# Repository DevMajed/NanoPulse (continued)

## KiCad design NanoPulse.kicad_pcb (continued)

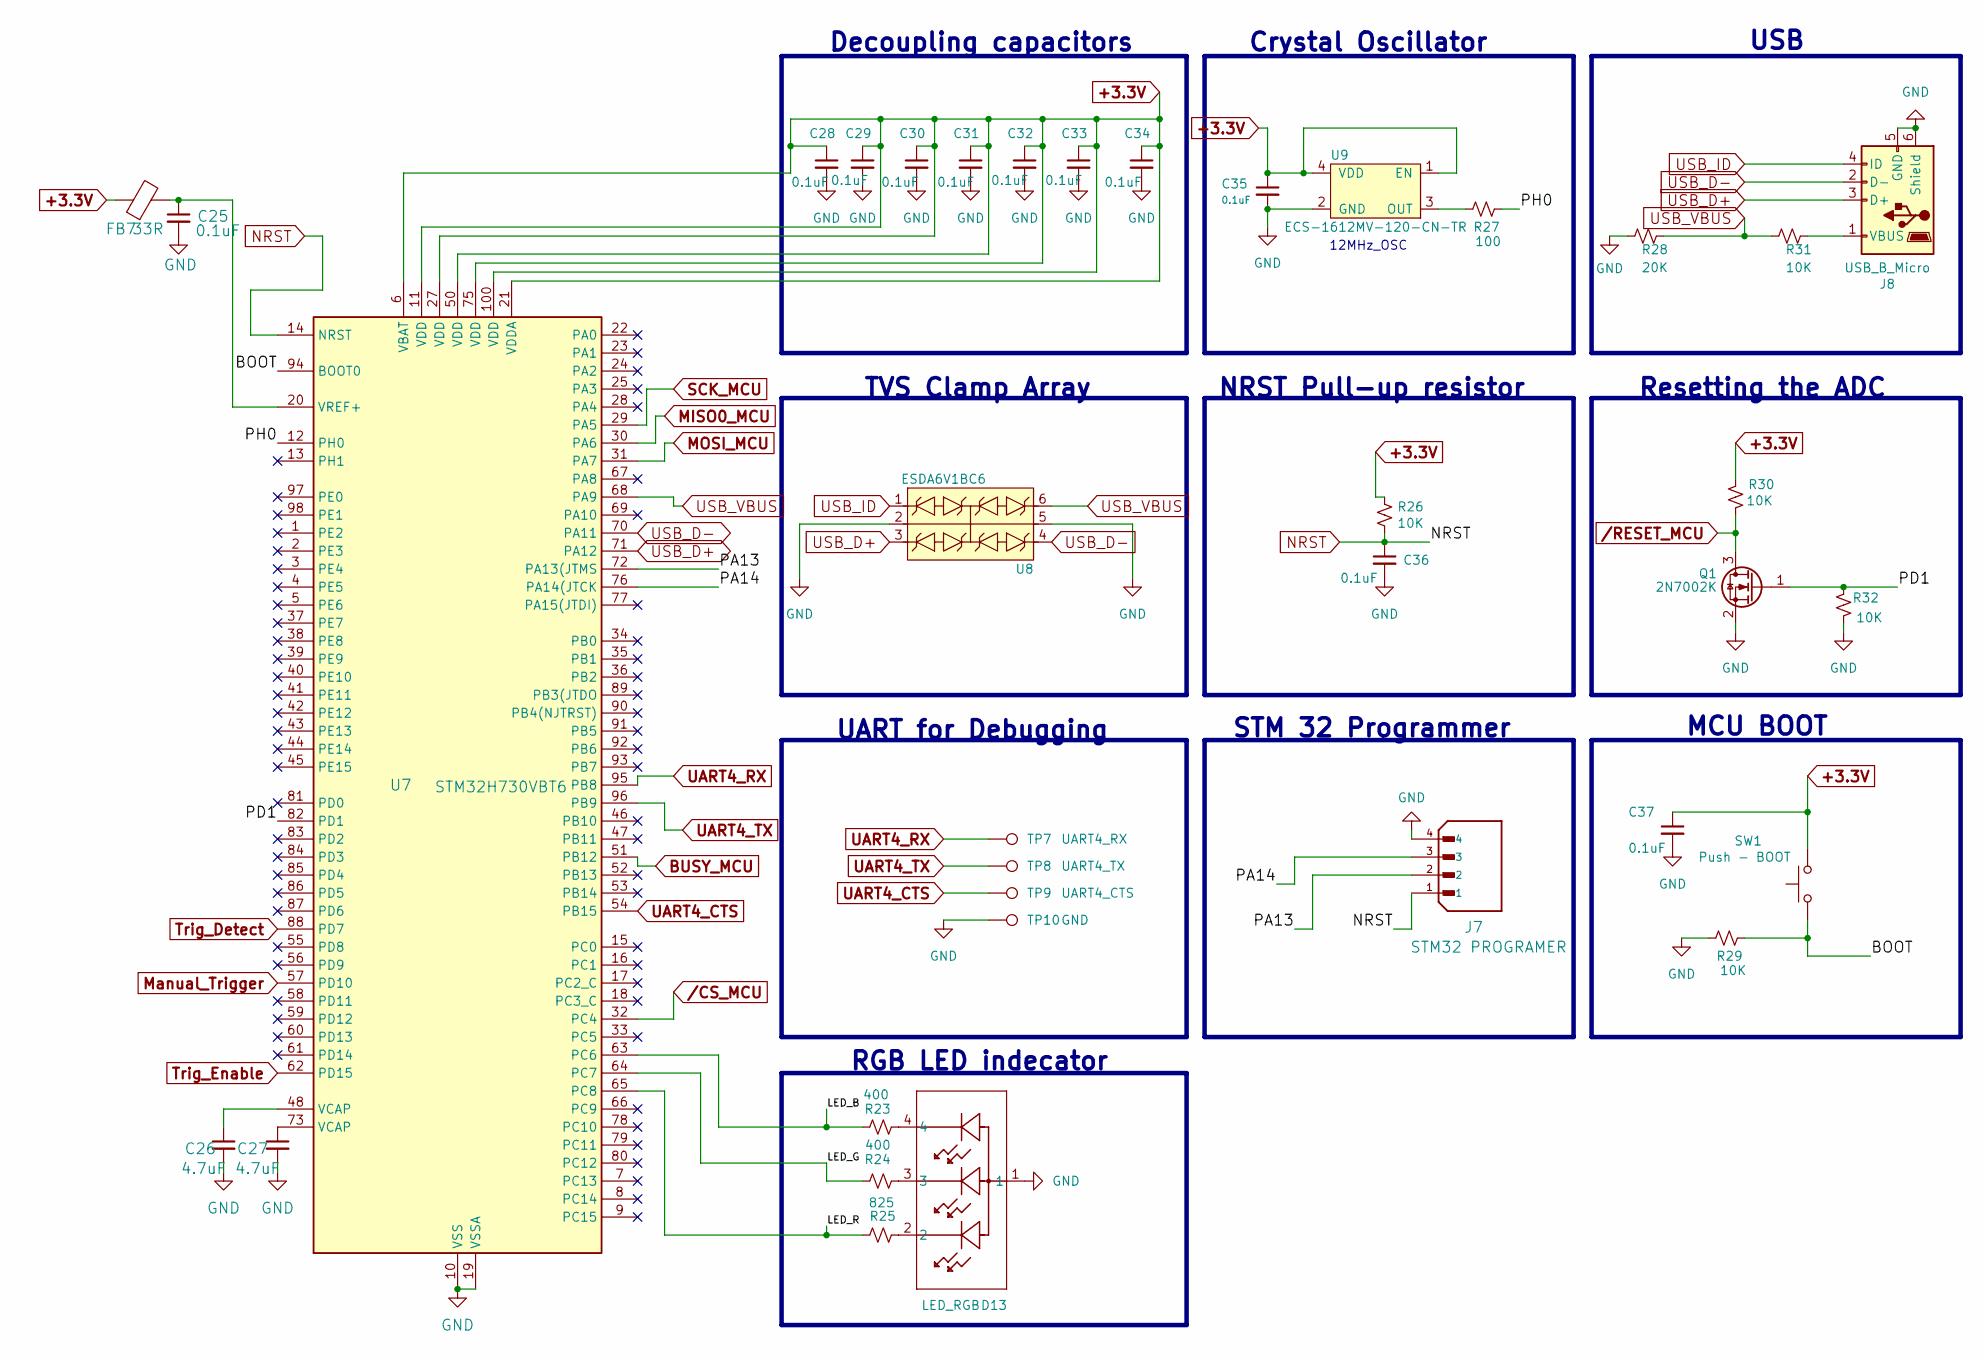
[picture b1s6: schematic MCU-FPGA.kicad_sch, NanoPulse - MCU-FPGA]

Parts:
C25, C28, C29, C30, C31, C32, C33, C34, C35, C36, C37: 0.1uF; C_0603_1608Metric; Mfg part # CC0603KRX7R7BB104; Digikey 311-1088-1-ND
C26, C27: 4.7uF; C_0805_2012Metric; Mfg part # CL21A475KAQNNNE; Digikey 1276-1244-1-ND
D13: LED_RGB; APHF1608SEEQBDZGKC_KNB-L; Mfg part # APHF1608SEEQBDZGKC; Digikey 754-2144-2-ND
FB7: 33R; L_0603_1608Metric_Pad1.05x0.95mm_HandSolder; Mfg part # BLM18PG330SN1D; Digikey 490-5220-1-ND
J7: STM32 PROGRAMER; SPARKFUN_PRT-14417; PARTREV NA; Digikey 1568-14417-ND
J8: USB_B_Micro; USB_Micro-B_Molex-105017-0001; Mfg part # 0473461001; Digikey WM11228CT-ND
Q1: 2N7002K; SOT-23; Mfg part # 2N7002LT1G; Digikey 2N7002LT1GOSCT-ND
R23, R24: 400; R_0603_1608Metric; Mfg part # PAT0603E4000BST1; Digikey PAT400ACT-ND
R25: 825; R_0603_1608Metric; Mfg part # RC0603FR-07825RL; Digikey 311-825HRCT-ND
R26, R29, R30, R31, R32: 10K; R_0603_1608Metric; Mfg part # RC0603FR-0710KL; Digikey 311-10.0KHRCT-ND
R27: 100; R_0603_1608Metric; Mfg part # RC0603FR-07100RL; Digikey 311-100HRCT-ND
R28: 20K; R_0603_1608Metric; Mfg part # RC0603FR-0720KL; Digikey 311-20.0KHRCT-ND
SW1: Push - BOOT; SW_Tactile_SPST_NO_Straight_CK_PTS636Sx25SMTRLFS; Mfg part # TL59NF160Q; Digikey EG2532CT-ND
TP7: UART4_RX; TestPoint_Pad_1.0x1.0mm
TP8: UART4_TX; TestPoint_Pad_1.0x1.0mm
TP9: UART4_CTS; TestPoint_Pad_1.0x1.0mm
TP10: GND; TestPoint_Pad_1.0x1.0mm
U7: STM32H730VBT6; LQFP-100_14x14mm_P0.5mm; Mfg part # STM32H730VBT6; Digikey 497-STM32H730VBT6-ND
U8: ESDA6V1BC6; SOT-23-6; Mfg part # STMicroelectronics; Digikey 497-6635-1-ND
U9: ECS-1612MV-120-CN-TR; Mfg part # ECS-1612MV-120-CN-TR; Digikey XC2833CT-ND

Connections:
+3.3V: C28.1, C29.1, C30.1, C31.1, C32.1, C33.1, C34.1, C35.1, C37.1, FB7.1, R26.1, R30.1, SW1.2, U7.6 (VBAT), U7.11 (VDD), U7.21 (VDDA), U7.27 (VDD), U7.50 (VDD), U7.75 (VDD), U7.100 (VDD), U9.1 (EN), U9.4 (VDD); also elsewhere on the board
/MCU-FPGA/BOOT: R29.1, SW1.1, U7.94 (BOOT0)
/MCU-FPGA/LED_B: R23.1, U7.63 (PC6)
/MCU-FPGA/LED_G: R24.1, U7.64 (PC7)
/MCU-FPGA/LED_R: R25.1, U7.65 (PC8)
/MCU-FPGA/PA13: J7.2, U7.72 (PA13(JTMS)
/MCU-FPGA/PA14: J7.3, U7.76 (PA14(JTCK)
/MCU-FPGA/PD1: Q1.1 (G), R32.1, U7.82 (PD1)
/MCU-FPGA/PH0: R27.1, U7.12 (PH0)
BUSY_MCU: U7.51 (PB12); also elsewhere on the board
GND: C25.2, C26.2, C27.2, C28.2, C29.2, C30.2, C31.2, C32.2, C33.2, C34.2, C35.2, C36.2, C37.2, D13.1, J7.4, J8.5 (GND), J8.6 (Shield), Q1.2 (S), R28.2, R29.2, R32.2, TP10.1, U7.10 (VSS), U7.19 (VSSA), U7.26 (VSS), U7.49 (VSS), U7.74 (VSS), U7.99 (VSS), U8.2, U8.5, U9.2 (GND); also elsewhere on the board
MISO0_MCU: U7.30 (PA6); also elsewhere on the board
MOSI_MCU: U7.31 (PA7); also elsewhere on the board
Manual_Trigger: U7.57 (PD10); also elsewhere on the board
NRST: C36.1, J7.1, R26.2, U7.14 (NRST)
unnamed: C26.1, U7.48 (VCAP)
unnamed: C27.1, U7.73 (VCAP)
unnamed: D13.2, R25.2
unnamed: D13.3, R24.2
unnamed: D13.4, R23.2
unnamed: J8.1 (VBUS), R31.1
unnamed: C25.1, FB7.2, U7.20 (VREF+)
unnamed: R27.2, U9.3 (OUT)
SCK_MCU: U7.29 (PA5); also elsewhere on the board
Trig_Detect: U7.88 (PD7); also elsewhere on the board
Trig_Enable: U7.62 (PD15); also elsewhere on the board
UART4_CTS: TP9.1, U7.54 (PB15)
UART4_RX: TP7.1, U7.95 (PB8)
UART4_TX: TP8.1, U7.96 (PB9)
USB_D+: J8.3 (D+), U7.71 (PA12), U8.3
USB_D-: J8.2 (D-), U7.70 (PA11), U8.4
USB_ID: J8.4 (ID), U8.1
USB_VBUS: R28.1, R31.2, U7.68 (PA9), U8.6
/CS_MCU: U7.32 (PC4); also elsewhere on the board
/RESET_MCU: Q1.3 (D), R30.2; also elsewhere on the board

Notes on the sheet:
NRST Pull-up resistor
MCU BOOT
STM 32 Programmer
USB
RGB LED indecator
12MHz_OSC
Decoupling capacitors
TVS Clamp Array
UART for Debugging
Resetting the ADC
Crystal Oscillator

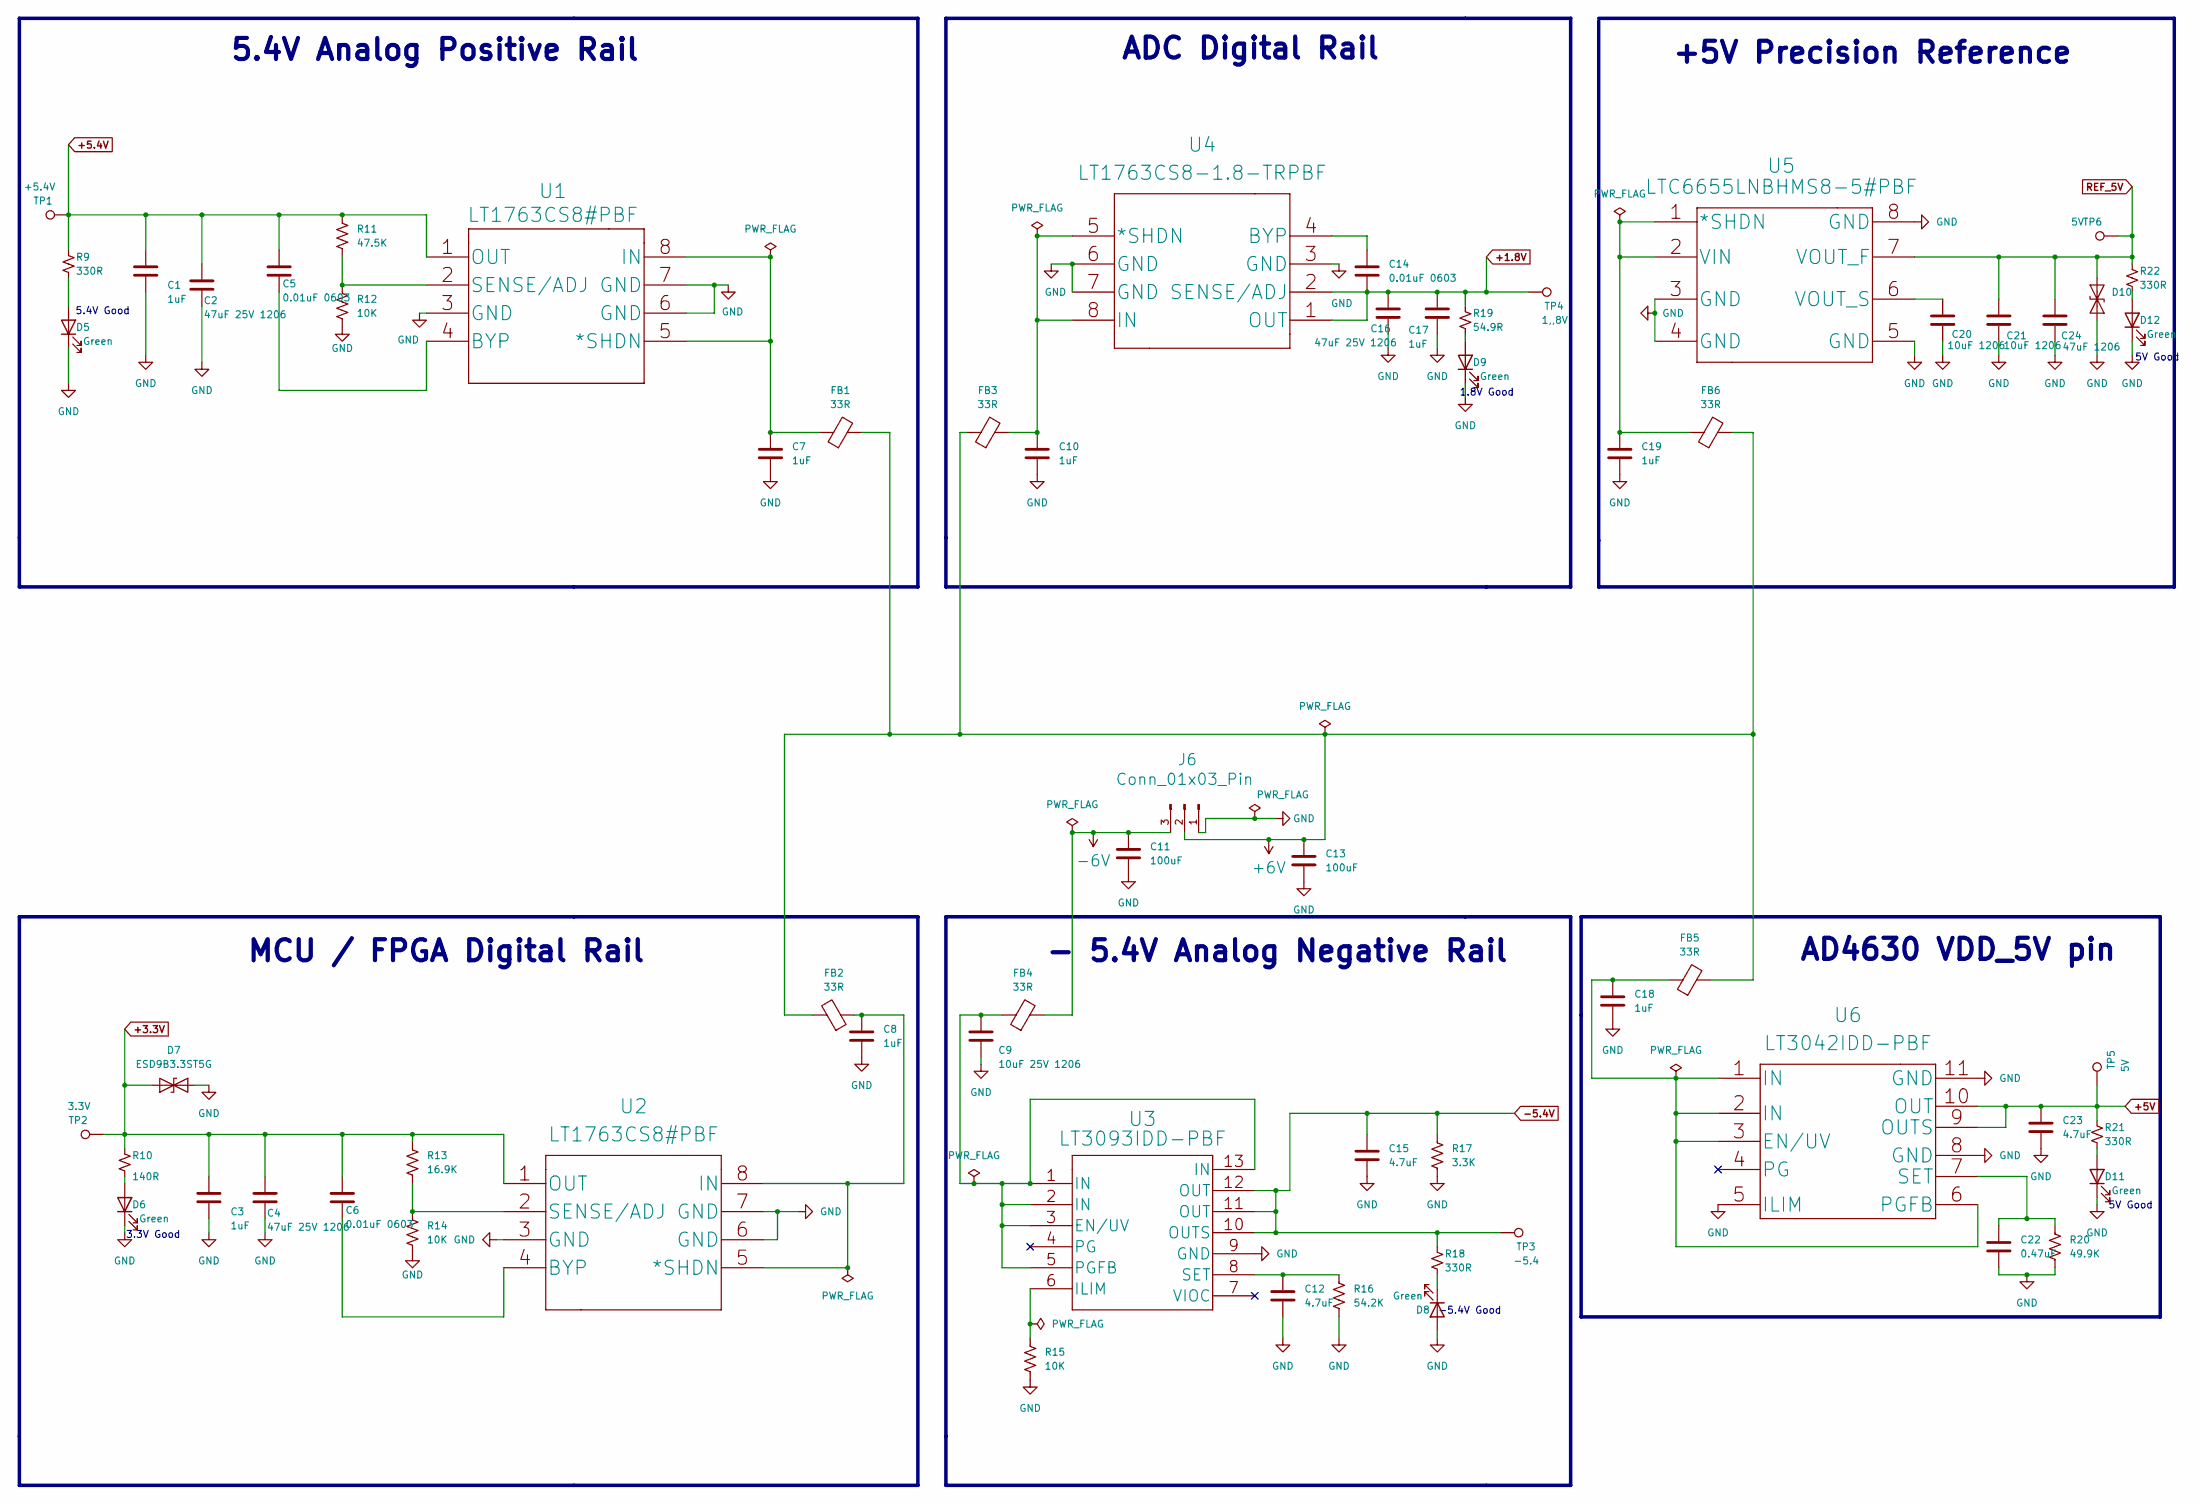
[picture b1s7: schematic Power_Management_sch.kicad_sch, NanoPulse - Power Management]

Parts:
C1, C3, C7, C8, C10, C17, C18, C19: 1uF; C_0603_1608Metric; Mfg part # CL10B105KP8NNNC; Digikey 1276-1946-1-ND
C2, C4, C16: 47uF 25V 1206; C_1206_3216Metric; Mfg part # GMC31X5R476M25NT; Digikey 4713-GMC31X5R476M25NTCT-ND
C5, C6, C14: 0.01uF 0603; C_0603_1608Metric; Mfg part # C0603C103J5REC7411; Digikey 399-17568-1-ND
C9: 10uF 25V 1206; C_1206_3216Metric; Mfg part # CL31A106MAHNNNE; Digikey 1276-1181-1-ND
C11, C13: 100uF; CP_EIA-3528-21_Kemet-B; Mfg part # TPSB107K006R0400; Digikey 478-4976-1-ND - Cut Tape
C12, C15, C23: 4.7uF; C_0805_2012Metric; Mfg part # CL21A475KAQNNNE; Digikey 1276-1244-1-ND
C20, C21: 10uF 1206; C_1206_3216Metric; Mfg part # CL31A106MAHNNNE; Digikey 1276-1181-1-ND
C22: 0.47uF; C_0805_2012Metric; Mfg part # CL21B474KAFNNNG; Digikey 1276-6480-1-ND
C24: 47uF 1206; C_1206_3216Metric; Mfg part # GMC31X5R476M25NT; Digikey 4713-GMC31X5R476M25NTCT-ND
D5, D6, D8, D9, D11, D12: Green; LED_0603_1608Metric; Mfg part # LTST-C191KGKT; Digikey 160-1446-1-ND
D7: ESD9B3.3ST5G; D_SOD-923; Mfg part # ESD9B3.3ST5G; Digikey ESD9B3.3ST5GOSCT-ND
D10: ESD9B5.0ST5G; D_SOD-923; Mfg part # ESD9B5.0ST5G; Digikey ESD9B5.0ST5GOSCT-ND - Cut Tape
FB1, FB2, FB3, FB4, FB5, FB6: 33R; L_0603_1608Metric_Pad1.05x0.95mm_HandSolder; Mfg part # BLM18PG330SN1D; Digikey 490-5220-1-ND
J6: Conn_01x03_Pin; PhoenixContact_MC_1,5_3-G-3.5_1x03_P3.50mm_Horizontal; Mfg part # PRPC003SAAN-RC; Digikey S1011EC-03-ND
R9, R18, R21, R22: 330R; R_0603_1608Metric; Mfg part # CRGP0603F330R; Digikey A130410CT-ND
R10: 140R; R_0603_1608Metric; Mfg part # ERJ-3EKF1400V; Digikey P140HCT-ND
R11: 47.5K; R_0603_1608Metric; Mfg part # RC0603FR-071KL; Digikey 311-47.5KHRCT-ND
R12, R14, R15: 10K; R_0603_1608Metric; Mfg part # RC0603FR-0710KL; Digikey 311-10.0KHRCT-ND
R13: 16.9K; R_0603_1608Metric; Mfg part # RMCF0603FT16K9; Digikey RMCF0603FT16K9CT-ND
R16: 54.2K; R_0603_1608Metric; Mfg part # RN73H1JTTD5422B25; Digikey 2019-RN73H1JTTD5422B25CT-ND
R17: 3.3K; R_0603_1608Metric; Mfg part # RC0603FR-073K3L; Digikey 311-3.30KHRCT-ND
R19: 54.9R; R_0603_1608Metric; Mfg part # RC0603FR-0754R9L; Digikey 311-54.9HRCT-ND
R20: 49.9K; R_0603_1608Metric; Mfg part # RC0603FR-0756KL; Digikey 311-56KHRCT-ND
TP1: +5.4V; TestPoint_Pad_1.0x1.0mm
TP2: 3.3V; TestPoint_Pad_1.0x1.0mm
TP3: -5.4; TestPoint_Pad_1.0x1.0mm
TP4: 1,,8V; TestPoint_Pad_1.0x1.0mm
TP5, TP6: 5V; TestPoint_Pad_1.0x1.0mm
U1, U2: LT1763CS8#PBF; SO-8_S_LIT-L; Mfg part # LT1763CS8#PBF; Digikey 505-LT1763CS8#PBF-ND
U3: LT3093IDD-PBF; 05-08-1725_ADI; Mfg part # LT3093IDD#PBF; Digikey 505-LT3093IDD#PBF-ND
U4: LT1763CS8-1.8-TRPBF; SO-8_S_LIT; Mfg part # LT1763CS8-1.8#TRPBF; Digikey 505-LT1763CS8-1.8#TRPBFCT-ND
U5: LTC6655LNBHMS8-5#PBF; MSOP-8_MS_LIT-L; Mfg part # LTC6655LNBHMS8-5#PBF; Digikey 505-LTC6655LNBHMS8-5#PBF-ND
U6: LT3042IDD-PBF; DFN-10_DD_LIT; Mfg part # LT3042IDD#TRPBF; Digikey LT3042IDD#TRPBFCT-ND

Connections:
+1.8V: C14.2, C16.1, C17.1, R19.1, TP4.1, U4.1 (OUT), U4.2 (SENSE/ADJ); also elsewhere on the board
+3.3V: C3.1, C4.1, C6.1, D7.1 (A1), R10.1, R13.1, TP2.1, U2.1 (OUT); also elsewhere on the board
+5.4V: C1.1, C2.1, C5.1, R9.1, R11.1, TP1.1, U1.1 (OUT); also elsewhere on the board
+5V: C23.2, R21.1, TP5.1, U6.9 (OUTS), U6.10 (OUT); also elsewhere on the board
+6V: C13.1, FB1.2, FB2.2, FB3.1, FB5.2, FB6.2, J6.2
-5.4V: C15.1, R17.1, R18.1, TP3.1, U3.10 (OUTS), U3.11 (OUT), U3.12 (OUT); also elsewhere on the board
-6V: C11.1, FB4.2, J6.3
GND: C1.2, C2.2, C3.2, C4.2, C7.2, C8.2, C9.2, C10.2, C11.2, C12.2, C13.2, C15.2, C16.2, C17.2, C18.2, C19.2, C20.2, C21.2, C22.1, C23.1, C24.2, D5.1 (K), D6.1 (K), D7.2 (A2), D8.2 (A), D9.1 (K), D10.2 (A2), D11.1 (K), D12.1 (K), J6.1, R12.2, R14.2, R15.2, R16.2, R17.2, R20.1, U1.3 (GND), U1.6 (GND), U1.7 (GND), U2.3 (GND), U2.6 (GND), U2.7 (GND), U3.9 (GND), U4.3 (GND), U4.6 (GND), U4.7 (GND), U5.3 (GND), U5.4 (GND), U5.5 (GND), U5.8 (GND), U6.5 (ILIM), U6.8 (GND), U6.11 (GND); also elsewhere on the board
unnamed: D5.2 (A), R9.2
unnamed: D6.2 (A), R10.2
unnamed: D8.1 (K), R18.2
unnamed: D9.2 (A), R19.2
unnamed: D11.2 (A), R21.2
unnamed: D12.2 (A), R22.2
unnamed: C7.1, FB1.1, U1.5 (*SHDN), U1.8 (IN)
unnamed: C5.2, U1.4 (BYP)
unnamed: R11.2, R12.1, U1.2 (SENSE/ADJ)
unnamed: C8.1, FB2.1, U2.5 (*SHDN), U2.8 (IN)
unnamed: C6.2, U2.4 (BYP)
unnamed: R13.2, R14.1, U2.2 (SENSE/ADJ)
unnamed: C9.1, FB4.1, U3.1 (IN), U3.2 (IN), U3.3 (EN/UV), U3.5 (PGFB), U3.13 (IN)
unnamed: R15.1, U3.6 (ILIM)
unnamed: C12.1, R16.1, U3.8 (SET)
unnamed: C10.1, FB3.2, U4.5 (*SHDN), U4.8 (IN)
unnamed: C14.1, U4.4 (BYP)
unnamed: C19.1, FB6.1, U5.1 (*SHDN), U5.2 (VIN)
unnamed: C20.1, U5.6 (VOUT_S)
unnamed: C18.1, FB5.1, U6.1 (IN), U6.2 (IN), U6.3 (EN/UV), U6.6 (PGFB)
unnamed: C22.2, R20.2, U6.7 (SET)
REF_5V: C21.1, C24.1, D10.1 (A1), R22.1, TP6.1, U5.7 (VOUT_F); also elsewhere on the board

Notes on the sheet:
-5.4V Good
ADC Digital Rail
MCU / FPGA Digital Rail
5.4V Analog Positive Rail
1.8V Good
- 5.4V Analog Negative Rail
AD4630 VDD_5V pin
5V Good
5.4V Good
3.3V Good
+5V Precision Reference

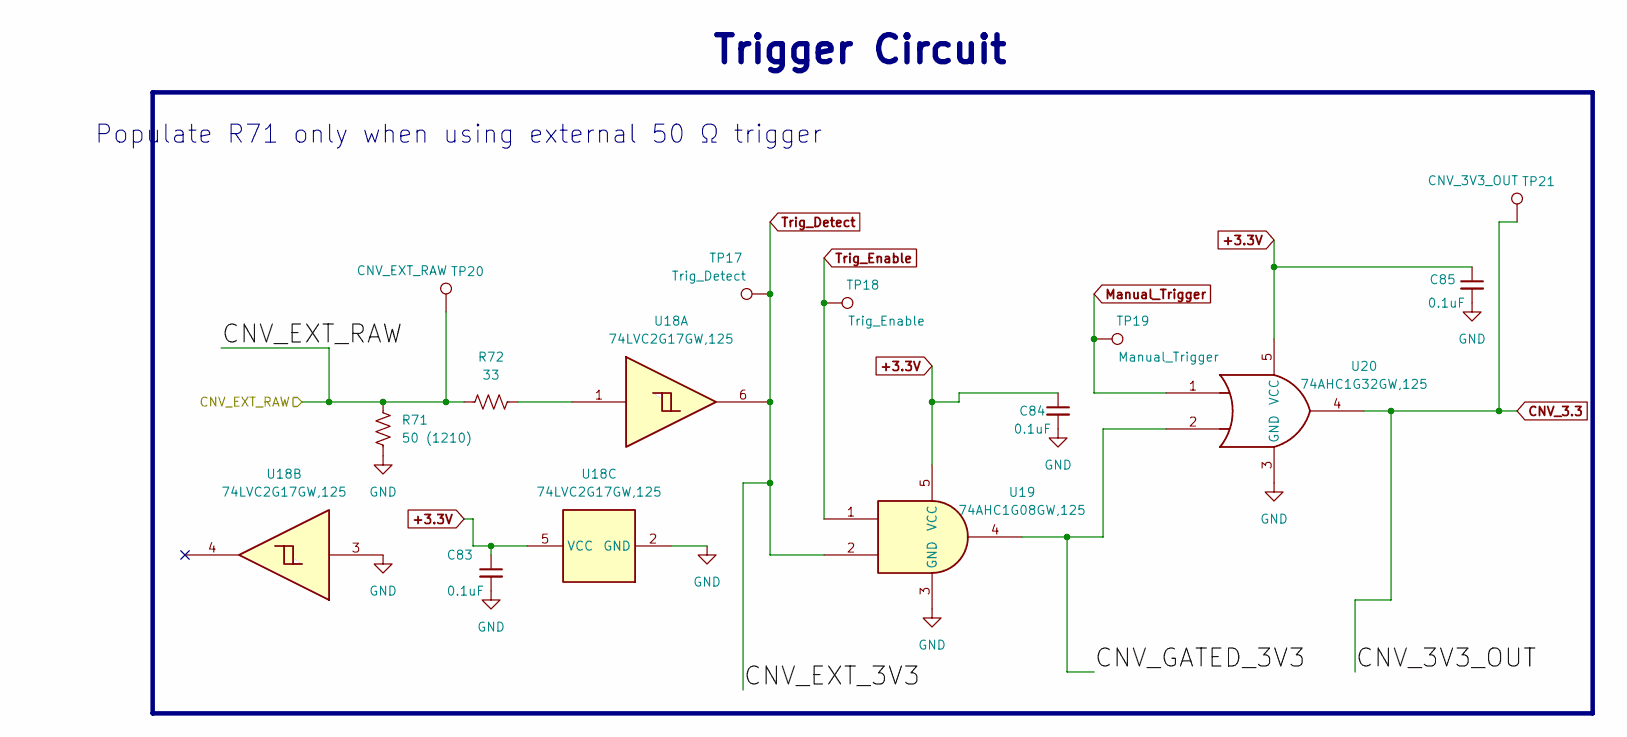
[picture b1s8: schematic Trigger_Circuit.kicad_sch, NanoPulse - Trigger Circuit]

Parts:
C83, C84, C85: 0.1uF; C_0603_1608Metric; Mfg part # CC0603KRX7R7BB104; Digikey 311-1088-1-ND
R71: 50 (1210); R_1210_3225Metric_Pad1.30x2.65mm_HandSolder; Mfg part # RCP1206W50R0JTP; Digikey 541-RCP1206W50R0JTPCT-ND
R72: 33; R_0603_1608Metric; Mfg part # RC0603FR-072KL; Digikey 311-33GRCT-ND
TP17: Trig_Detect; TestPoint_Pad_1.0x1.0mm
TP18: Trig_Enable; TestPoint_Pad_1.0x1.0mm
TP19: Manual_Trigger; TestPoint_Pad_1.0x1.0mm
TP20: CNV_EXT_RAW; TestPoint_Pad_1.0x1.0mm
TP21: CNV_3V3_OUT; TestPoint_Pad_1.0x1.0mm
U18: 74LVC2G17GW,125; SOT-363_SC-70-6; Mfg part # 74LVC2G17GW,125; Digikey 1727-4218-1-ND
U19: 74AHC1G08GW,125; SOT-353_SC-70-5; Mfg part # 74AHC1G08GW,125; Digikey 1727-3148-1-ND
U20: 74AHC1G32GW,125; SOT-353_SC-70-5; Mfg part # 74AHC1G32GW,125; Digikey 1727-3150-1-ND

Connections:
+3.3V: C83.1, C84.1, C85.1, U18.5 (VCC), U19.5 (VCC), U20.5 (VCC); also elsewhere on the board
/Trigger Circuit/CNV_EXT_RAW: R71.1, R72.2, TP20.1; also elsewhere on the board
/Trigger Circuit/CNV_GATED_3V3: U19.4, U20.2
CNV_3.3: TP21.1, U20.4; also elsewhere on the board
GND: C83.2, C84.2, C85.2, R71.2, U18.2 (GND), U18.3, U19.3 (GND), U20.3 (GND); also elsewhere on the board
Manual_Trigger: TP19.1, U20.1; also elsewhere on the board
unnamed: R72.1, U18.1
Trig_Detect: TP17.1, U18.6, U19.2; also elsewhere on the board
Trig_Enable: TP18.1, U19.1; also elsewhere on the board

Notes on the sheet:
Populate R71 only when using external 50 Ω trigger
Trigger Circuit

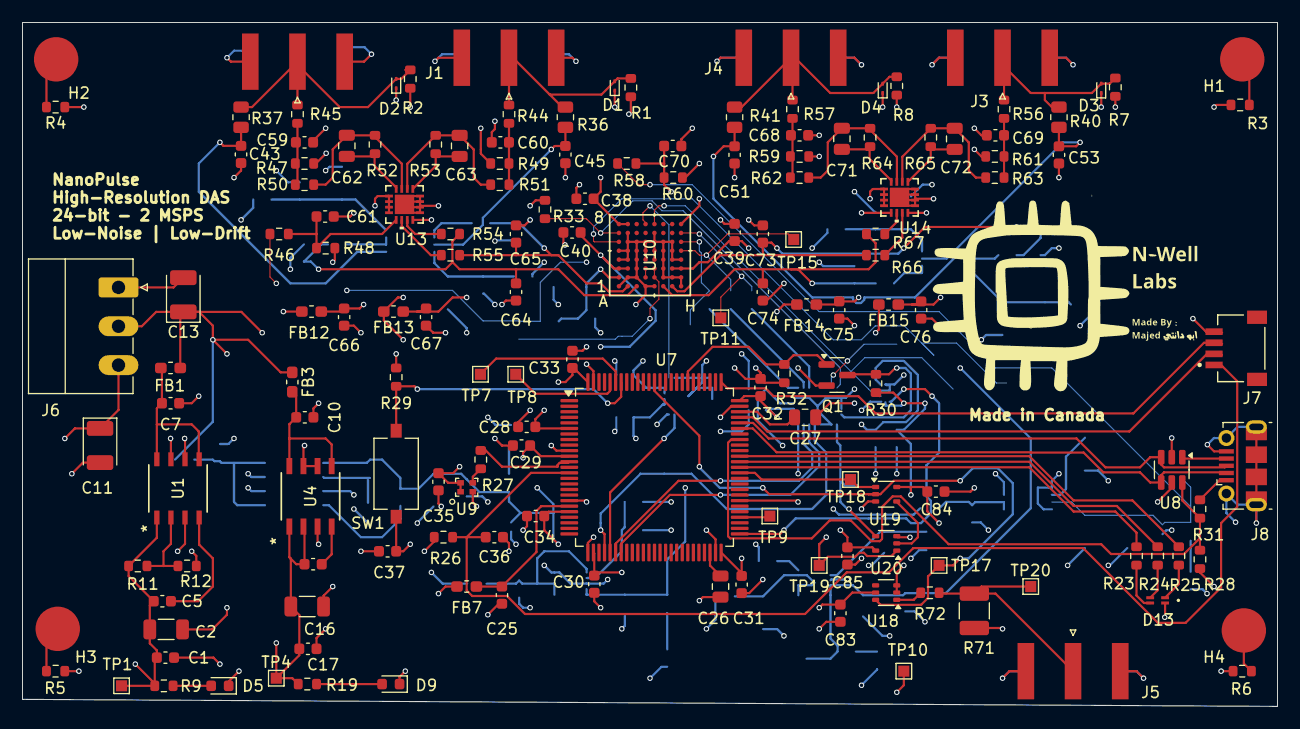
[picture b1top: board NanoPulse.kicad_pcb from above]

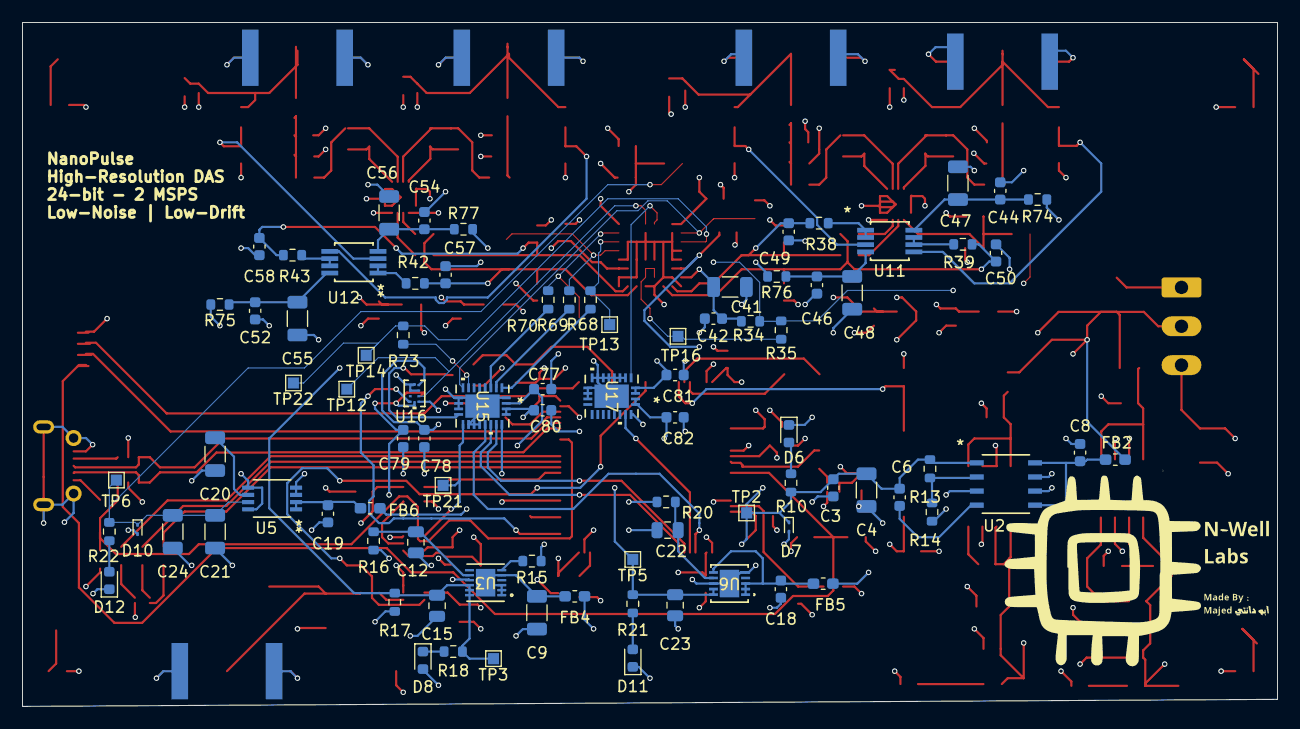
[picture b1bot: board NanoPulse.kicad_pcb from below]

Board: 4 copper layers, 113.0 x 61.6 mm, 244 parts (88 on the bottom side), 126 nets.

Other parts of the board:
Logo1#2: Majed's Logo; Logo_Majed_small

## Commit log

2025-07-12 Just completed the power management system
2025-07-15 edited Power management schematic
2025-08-10 All done, Gerberd out :)
2025-08-10 Extra signal conditioning
